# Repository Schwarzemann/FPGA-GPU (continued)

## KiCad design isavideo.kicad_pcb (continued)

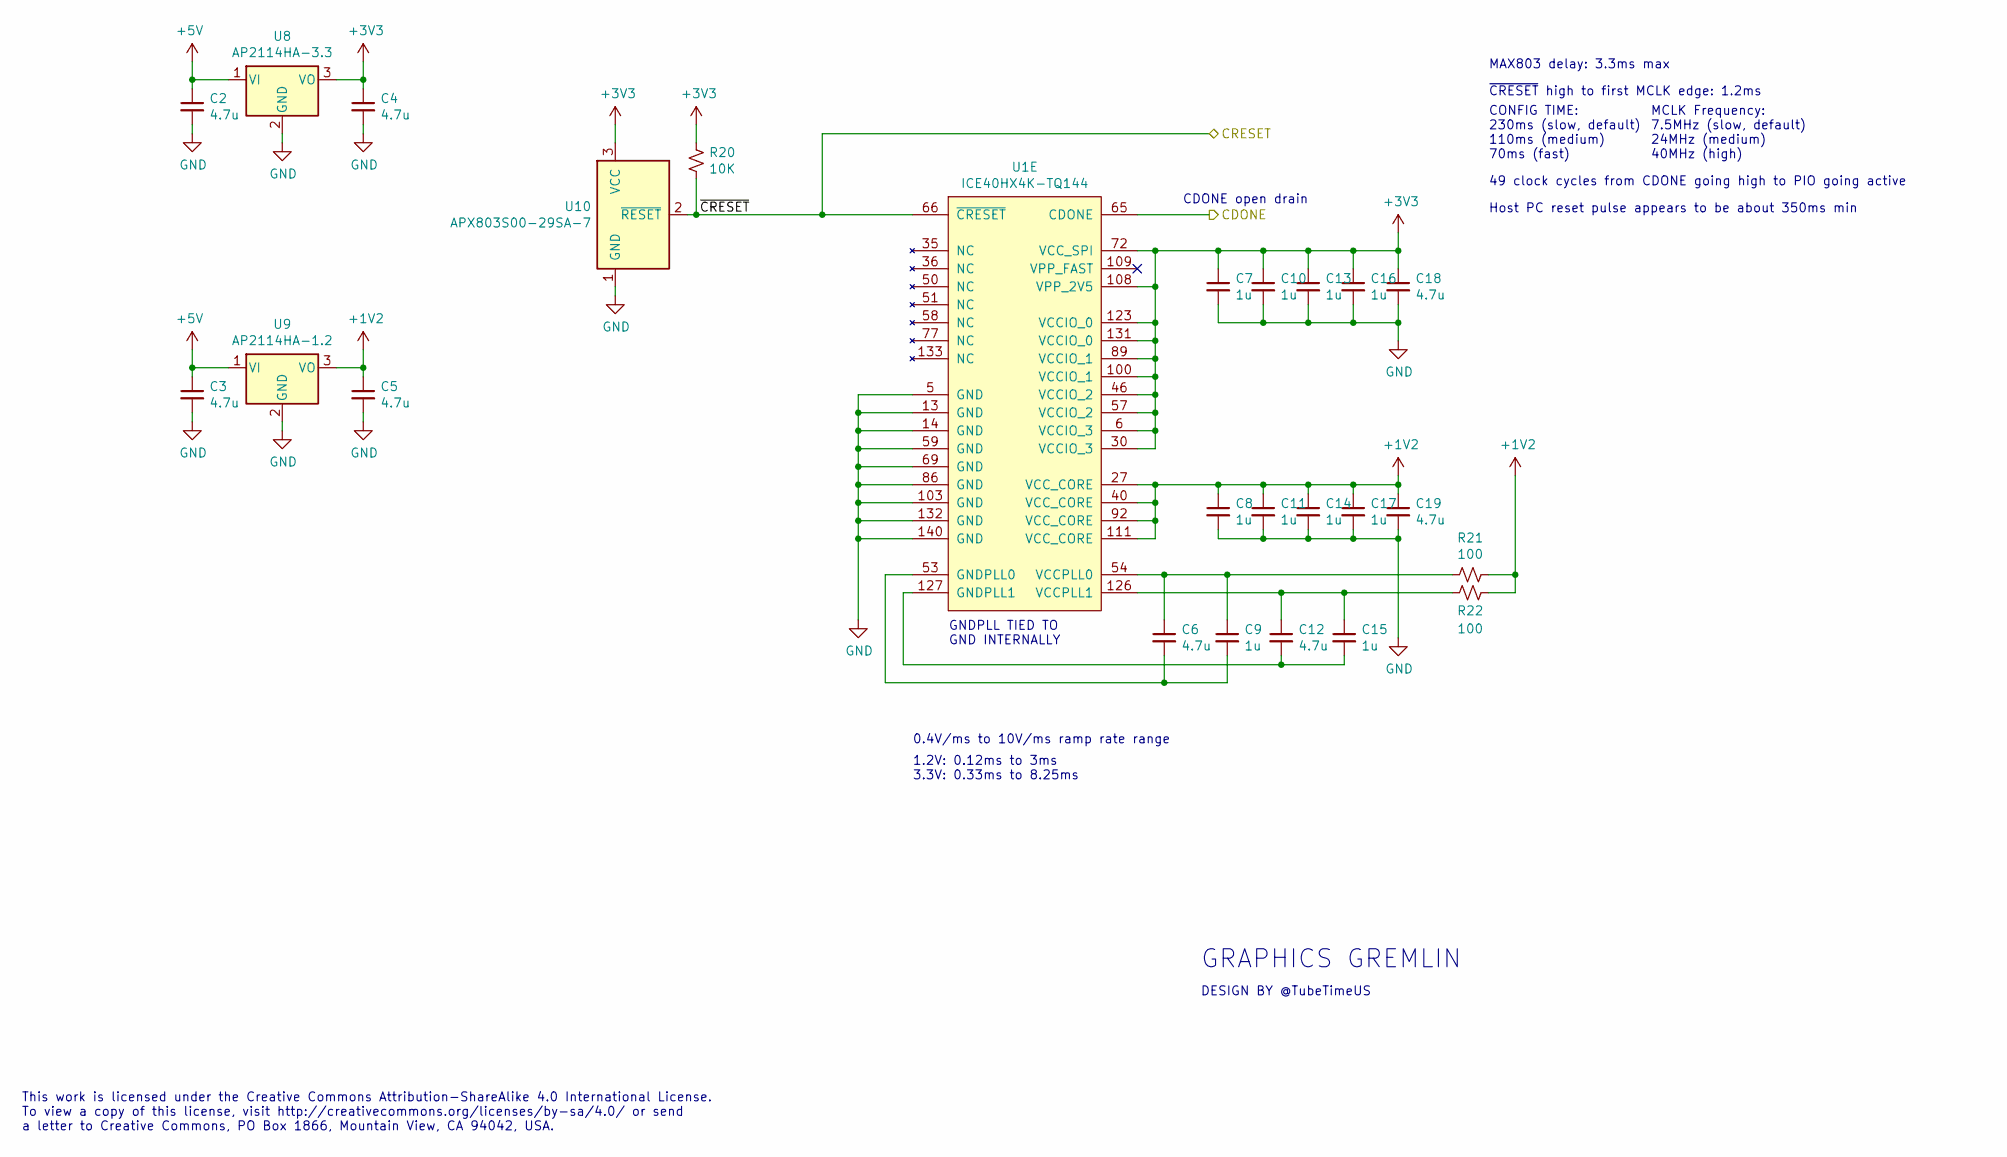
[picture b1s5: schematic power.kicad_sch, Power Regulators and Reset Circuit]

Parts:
C2, C3, C4, C5, C6, C12, C18, C19: 4.7u; CAPC1608X100; Mouser 187-CL10A475KP8NNNC
C7, C8, C9, C10, C11, C13, C14, C15, C16, C17: 1u; CAPC1608X100; Mouser 810-CGA3E1X7R1C105AC
R20: 10K; RESC1608X55; Mouser 603-RC0603FR-0710KL
R21, R22: 100; RESC1608X55; Mouser 603-RC0603FR-07100RL
U1: ICE40HX4K-TQ144; TSQFP50P2200X2200X160-144; Mouser 842-ICE40HX4K-TQ144
U8: AP2114HA-3.3; SOT230P700X170-3; Mouser 621-AP2114HA-3.3TRG1
U9: AP2114HA-1.2; SOT230P700X170-3; Mouser 621-AP2114HA-1.2TRG1
U10: APX803S00-29SA-7; SOT95P230X117-3; Mouser 621-APX803S00-29SA-7

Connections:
+1V2: C5.1, C8.1, C11.1, C14.1, C17.1, C19.1, R21.1, R22.1, U1.27 (VCC_CORE), U1.40 (VCC_CORE), U1.92 (VCC_CORE), U1.111 (VCC_CORE), U9.3 (VO)
+3V3: C4.1, C7.1, C10.1, C13.1, C16.1, C18.1, R20.1, U1.6 (VCCIO_3), U1.30 (VCCIO_3), U1.46 (VCCIO_2), U1.57 (VCCIO_2), U1.72 (VCC_SPI), U1.89 (VCCIO_1), U1.100 (VCCIO_1), U1.108 (VPP_2V5), U1.123 (VCCIO_0), U1.131 (VCCIO_0), U8.3 (VO), U10.3 (VCC); also elsewhere on the board
+5V: C2.1, C3.1, U8.1 (VI), U9.1 (VI); also elsewhere on the board
/CDONE: U1.65 (CDONE); also elsewhere on the board
/~CRESET: R20.2, U1.66 (~CRESET), U10.2 (~RESET); also elsewhere on the board
GND: C2.2, C3.2, C4.2, C5.2, C7.2, C8.2, C10.2, C11.2, C13.2, C14.2, C16.2, C17.2, C18.2, C19.2, U1.5 (GND), U1.13 (GND), U1.14 (GND), U1.59 (GND), U1.69 (GND), U1.86 (GND), U1.103 (GND), U1.132 (GND), U1.140 (GND), U8.2 (GND), U9.2 (GND), U10.1 (GND); also elsewhere on the board
unnamed: C6.1, C9.1, R21.2, U1.54 (VCCPLL0)
unnamed: C6.2, C9.2, U1.53 (GNDPLL0)
unnamed: C12.1, C15.1, R22.2, U1.126 (VCCPLL1)
unnamed: C12.2, C15.2, U1.127 (GNDPLL1)

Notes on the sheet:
49 clock cycles from CDONE going high to PIO going active
GNDPLL TIED TO GND INTERNALLY
0.4V/ms to 10V/ms ramp rate range
1.2V: 0.12ms to 3ms 3.3V: 0.33ms to 8.25ms
CONFIG TIME: 230ms (slow, default) 110ms (medium) 70ms (fast)
DESIGN BY @TubeTimeUS
Host PC reset pulse appears to be about 350ms min
MCLK Frequency: 7.5MHz (slow, default) 24MHz (medium) 40MHz (high)
MAX803 delay: 3.3ms max
This work is licensed under the Creative Commons Attribution-ShareAlike 4.0 International License. To view a copy of this license, visit http://creativecommons.org/licenses/by-sa/4.0/ or send a letter to Creative Commons, PO Box 1866, Mountain View, CA 94042, USA.
~{CRESET} high to first MCLK edge: 1.2ms
CDONE open drain
GRAPHICS GREMLIN

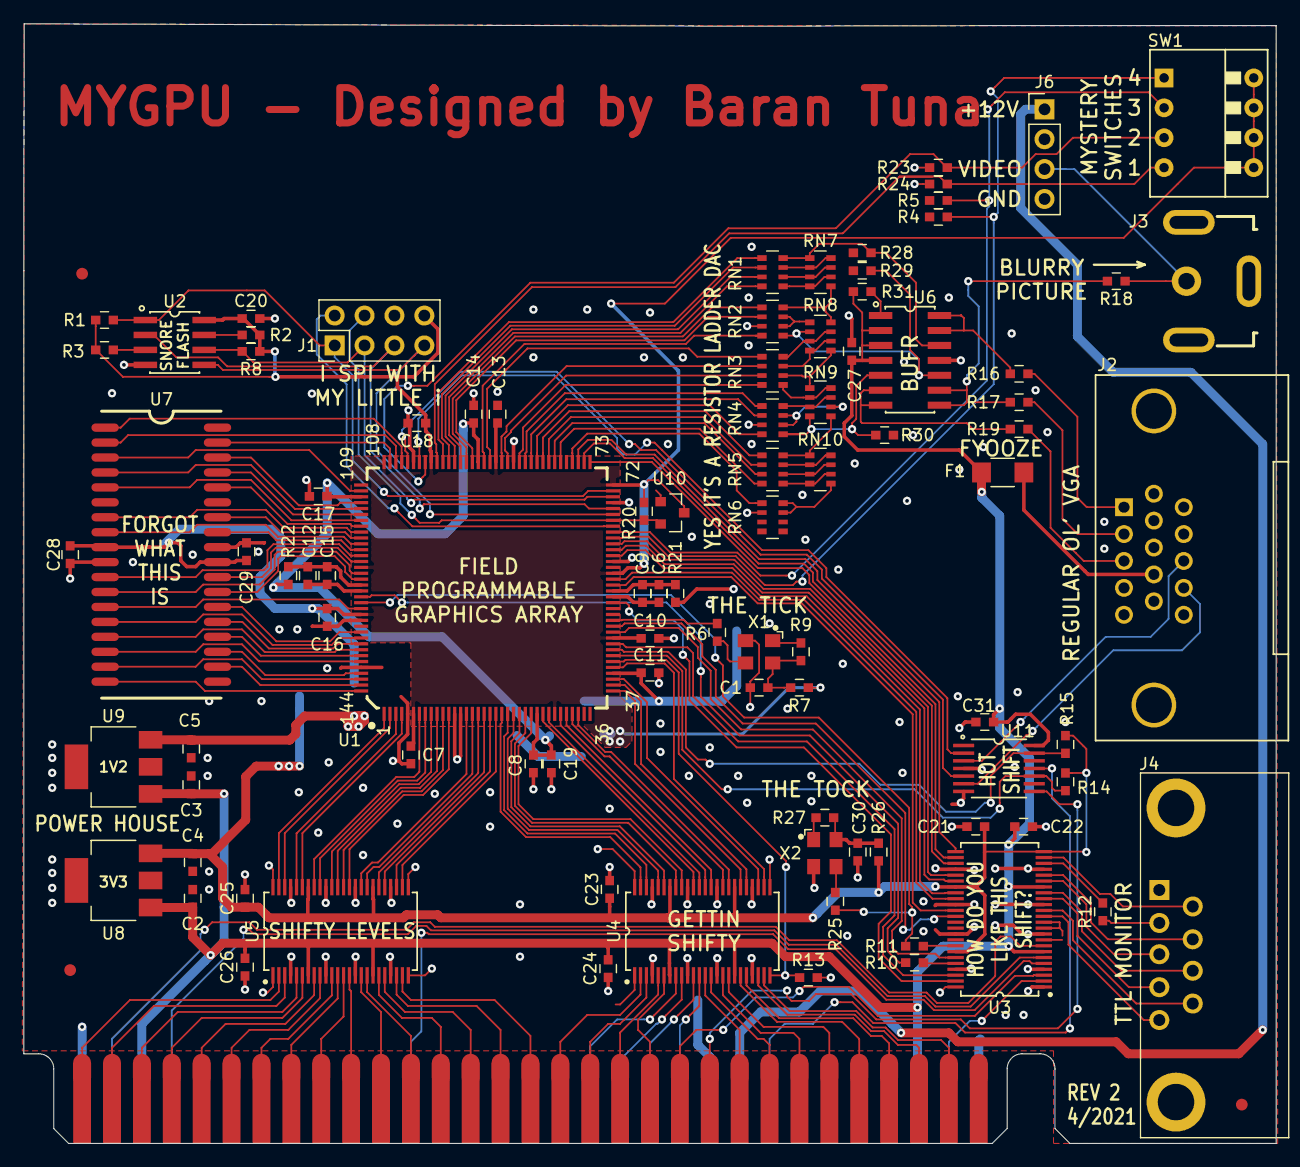
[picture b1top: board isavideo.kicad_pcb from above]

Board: 2 copper layers, 106.4 x 95.1 mm, 97 parts (0 on the bottom side), 206 nets.

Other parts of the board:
MH1: MNT_KEYSTONE_9200

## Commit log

2024-10-16 Screenshots
